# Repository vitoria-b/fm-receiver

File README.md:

# fm-receiver
Electronic Instrumentation subject project at Federal University of Santa Catarina.

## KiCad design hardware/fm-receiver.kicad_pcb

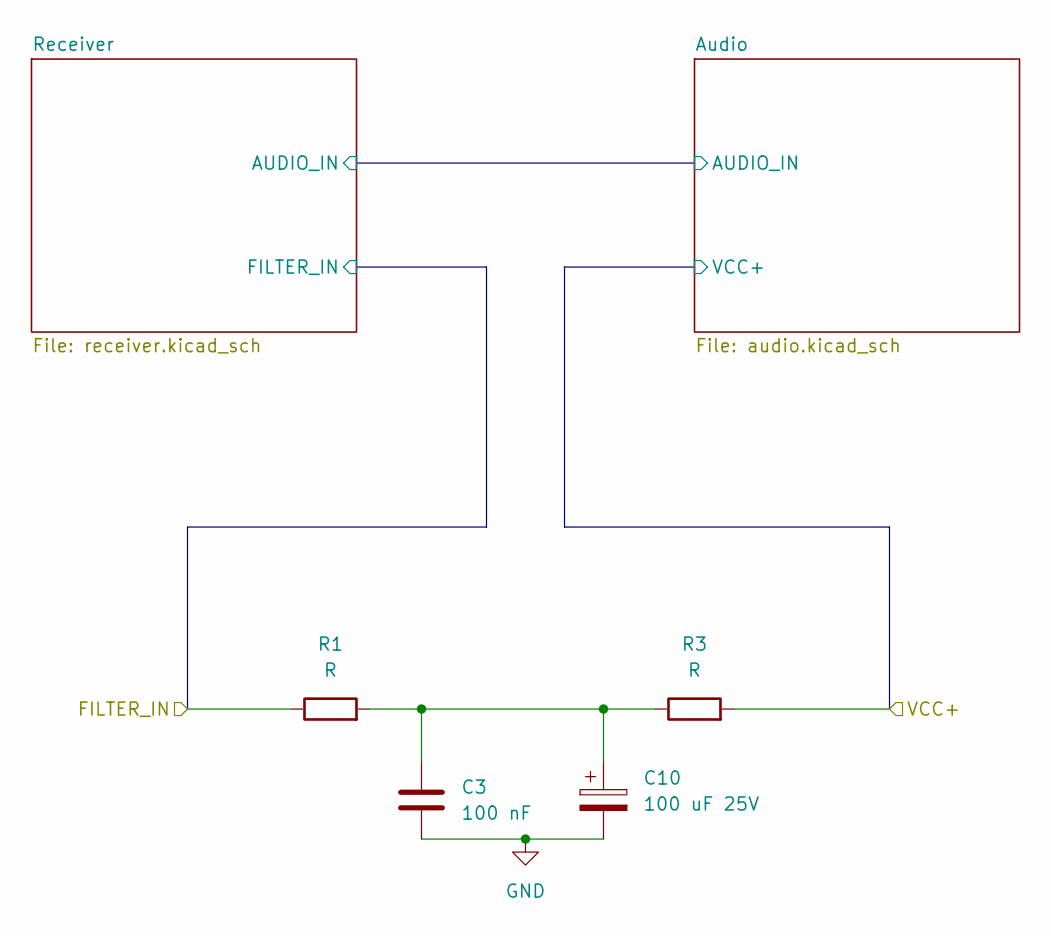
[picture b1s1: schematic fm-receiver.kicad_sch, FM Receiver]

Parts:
C3: 100 nF; C_Disc_D4.3mm_W1.9mm_P5.00mm
C10: 100 uF 25V; CP_Radial_D5.0mm_P2.50mm
R1, R3: R; R_Axial_DIN0207_L6.3mm_D2.5mm_P10.16mm_Horizontal

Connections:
/FILTER_IN: R1.1; also elsewhere on the board
/VCC+: R3.2; also elsewhere on the board
GND: C3.2, C10.2; also elsewhere on the board
unnamed: C3.1, C10.1, R1.2, R3.1

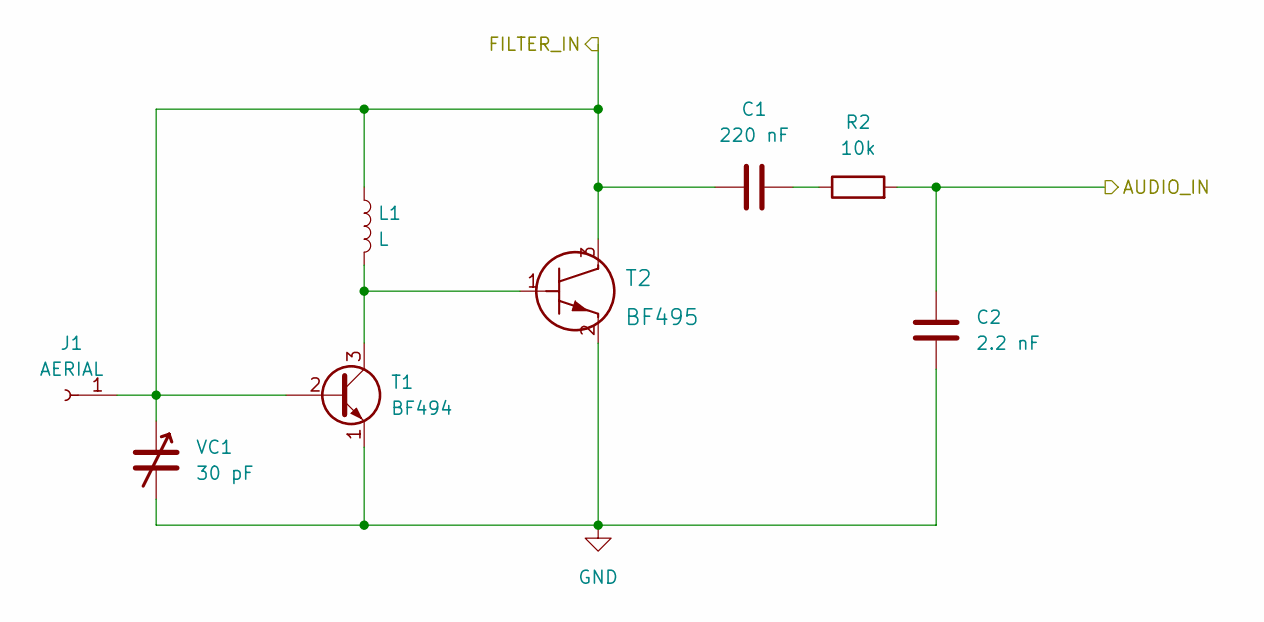
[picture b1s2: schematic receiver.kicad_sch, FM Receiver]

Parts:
C1: 220 nF; C_Disc_D4.3mm_W1.9mm_P5.00mm
C2: 2.2 nF; C_Disc_D4.3mm_W1.9mm_P5.00mm
J1: AERIAL; MountingHole_2.2mm_M2_DIN965_Pad
L1: L; L_Axial_L7.0mm_D3.3mm_P12.70mm_Horizontal_Fastron_MICC
R2: 10k; R_Axial_DIN0207_L6.3mm_D2.5mm_P10.16mm_Horizontal
T1: BF494; TO-39-3
T2: BF495; bf495
VC1: 30 pF; CP_Radial_Tantal_D5.0mm_P5.00mm

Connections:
/Audio/AUDIO_IN: C2.1, R2.2; also elsewhere on the board
/FILTER_IN: C1.1, J1.1, L1.1, T1.2 (B), T2.3, VC1.1; also elsewhere on the board
GND: C2.2, T1.1 (E), T2.2, VC1.2; also elsewhere on the board
unnamed: C1.2, R2.1
unnamed: L1.2, T1.3 (C), T2.1

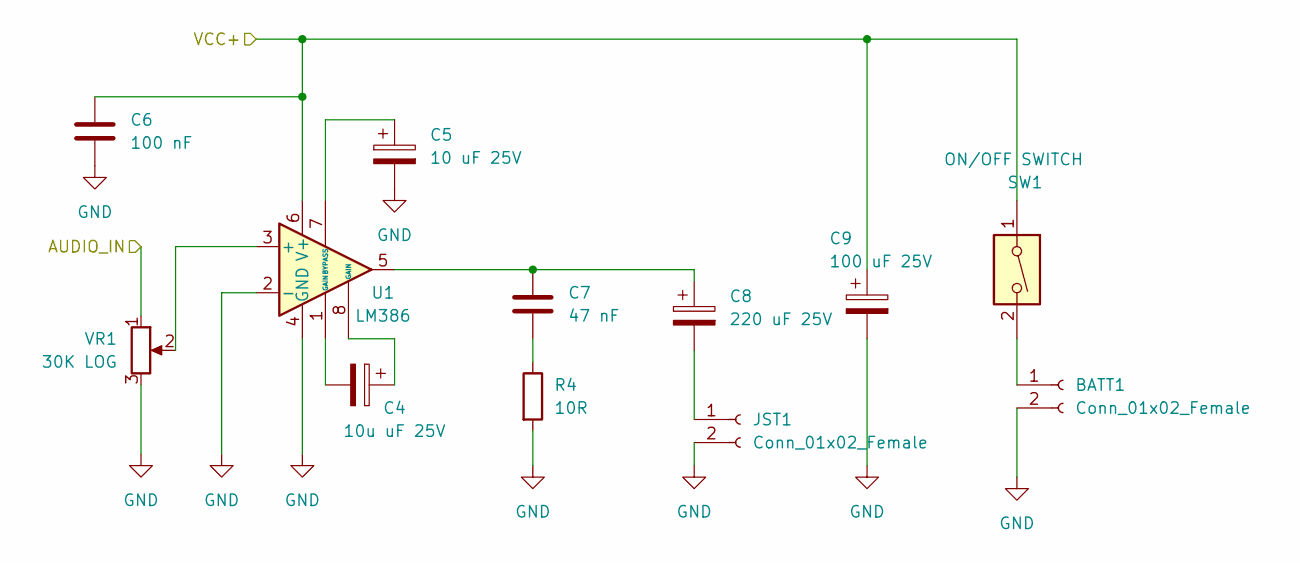
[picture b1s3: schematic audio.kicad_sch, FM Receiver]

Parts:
BATT1: Conn_01x02_Female; bf495
C4: 10u uF 25V; CP_Radial_D5.0mm_P2.50mm
C5: 10 uF 25V; CP_Radial_D5.0mm_P2.50mm
C6: 100 nF; C_Disc_D4.3mm_W1.9mm_P5.00mm
C7: 47 nF; C_Disc_D4.3mm_W1.9mm_P5.00mm
C8: 220 uF 25V; CP_Radial_D5.0mm_P2.50mm
C9: 100 uF 25V; CP_Radial_D5.0mm_P2.50mm
JST1: Conn_01x02_Female; L_Axial_L7.0mm_D3.3mm_P12.70mm_Horizontal_Fastron_MICC
R4: 10R; R_Axial_DIN0207_L6.3mm_D2.5mm_P10.16mm_Horizontal
SW1: ON/OFF SWITCH; L_Axial_L7.0mm_D3.3mm_P10.16mm_Horizontal_Fastron_MICC
U1: LM386; lm386
VR1: 30K LOG; TerminalBlock_bornier-3_P5.08mm

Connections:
/Audio/AUDIO_IN: VR1.1; also elsewhere on the board
/VCC+: C6.1, C9.1, SW1.1, U1.6 (V+); also elsewhere on the board
GND: BATT1.2, C5.2, C6.2, C9.2, JST1.2, R4.2, U1.2 (-), U1.4 (GND), VR1.3; also elsewhere on the board
unnamed: BATT1.1, SW1.2
unnamed: C4.1, U1.8 (GAIN)
unnamed: C4.2, U1.1 (GAIN)
unnamed: C5.1, U1.7 (BYPASS)
unnamed: C7.1, C8.1, U1.5
unnamed: C7.2, R4.1
unnamed: C8.2, JST1.1
unnamed: U1.3 (+), VR1.2

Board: 2 copper layers, 24 parts (0 on the bottom side), 15 nets, no tracks yet.

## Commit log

2024-11-04 hardware: finishing schematics
2024-11-04 hardware: updating library
2024-11-04 hardware: starting layout
2024-11-05 hardware: finishing layout
2024-11-05 hardware: adding some text to facilitate

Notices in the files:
parts and their libraries:
Copyright 2016 Accelerated Designs. All rights reserved.
